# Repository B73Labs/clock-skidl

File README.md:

# Skidl + KiCad + Freerouting Clock Example

## TODO
- Replace Freerouting with programmatic routing

## Components

- WS2813 LEDs

## Programs
- Skidl 0.0.22
- KiCad
- Freerouting/LayoutEditor
- PyCharm Community

## Clock Generation

- Generate clock.net

`./clock.py`

- Load netlist into pcbnew
  - Open pcbnew
  - Tools > Load Netlist
  - Load clock.net
  - Select Re-associate footprints by reference (if required)
  - Update PCB
  - Close
  - Save pcb
  - Close pcbnew

- Generate layout
`./clock_place_leds.py`

- Export DSN for Freerouting
  - Open pcbnew
  - Export > Spectra DSN - `clock.dsn`
  
- Auto routing
  - Open freerouting
  - Open Your Own Design - `clock.dsn`
  - click Autorouter
  - get a coffee
  - File > Export Specctra Session File
  - File > Save and Exit  
  - Open pcbnew
  - File > Import > Specctra Session `clock.ses`
  
## Screenshot

## References

- [Skidl docs](https://xesscorp.github.io/skidl/docs/_site/index.html)
- [KiCad Scripting Reference](https://github.com/KiCad/kicad-doc/blob/master/src/pcbnew/pcbnew_python_scripting.adoc)
- [Python Scripting Example: Studio Clock](https://forum.kicad.info/t/python-scripting-example-studio-clock/5387)
- Kevin Cuzner [Arranging components in a circle with KiCad](http://kevincuzner.com/tag/pcbnew/)
- Studio Clock source - [KiCadStudioClock.zip](https://kicad-info.s3-us-west-2.amazonaws.com/original/2X/4/49e167315a677e95bbfc2e08c05e37a0b8d94dea.zip)
- Skidl: Blinkenface - [Others use it, too!](https://xesscorp.github.io/skidl/docs/_site/blog/others-use-it-too)
- Miles McCoo [KiCad Scripting blog](https://kicad.mmccoo.com/)
- Skidl: Studio Clock - [Two Easy Pieces](https://xesscorp.github.io/skidl/docs/_site/blog/two-easy-pieces)
- [LayoutEditor](http://www.layouteditor.net/)

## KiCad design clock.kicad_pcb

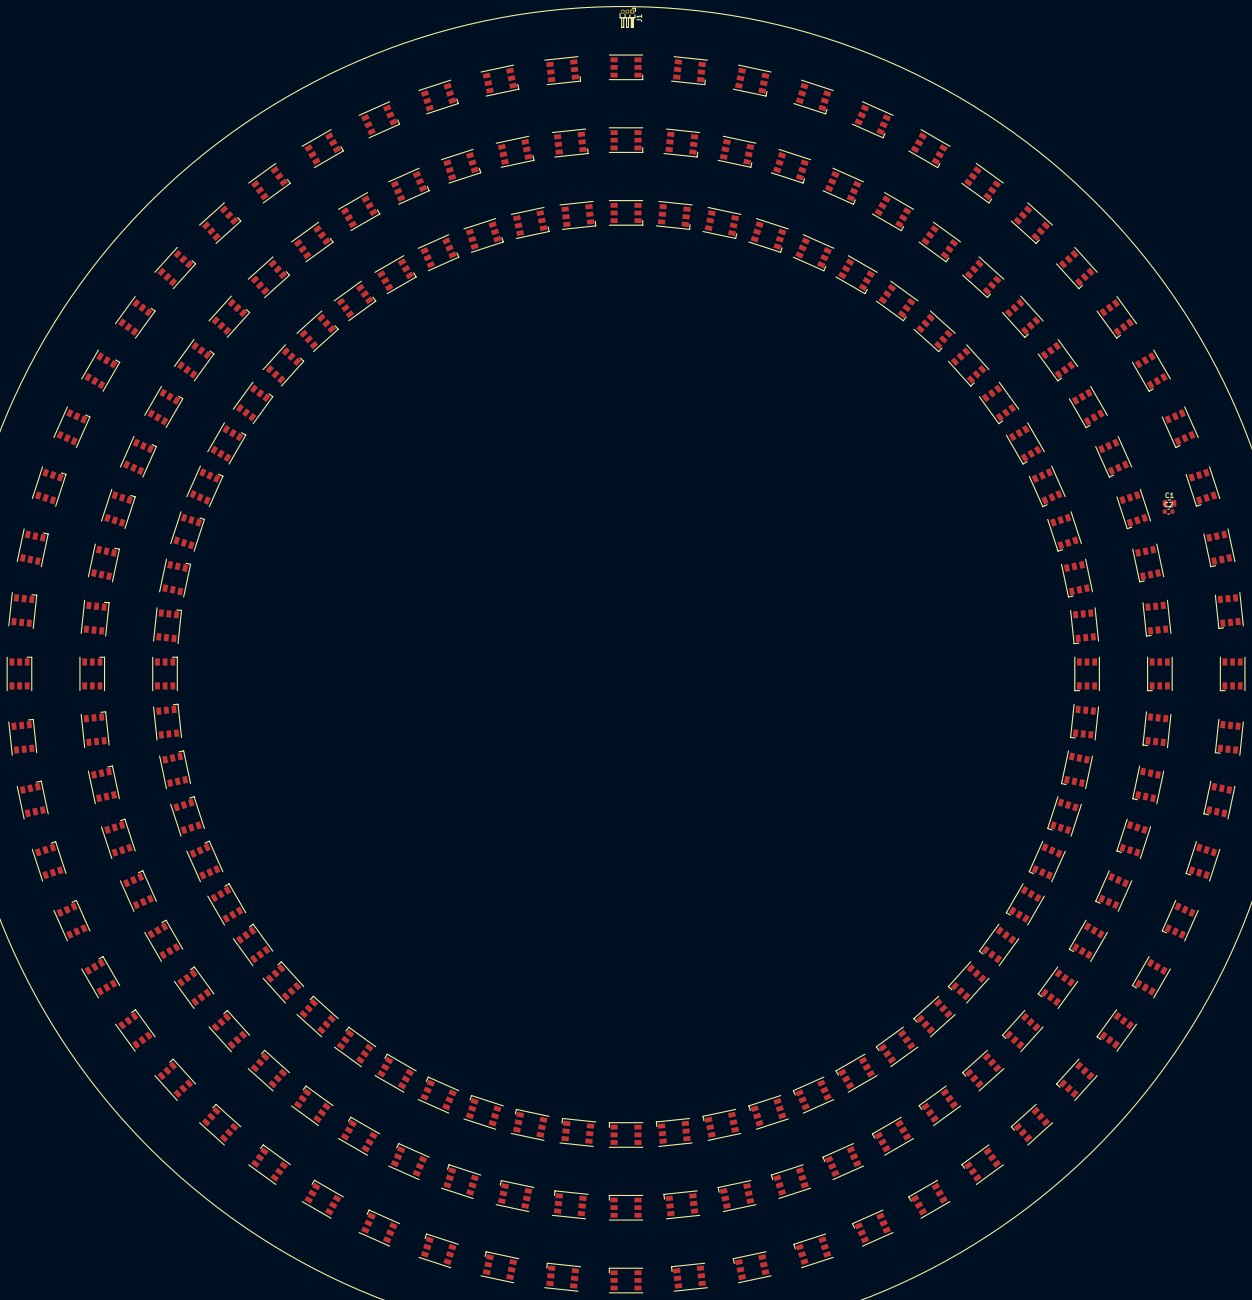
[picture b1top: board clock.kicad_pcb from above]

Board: 2 copper layers, 183 parts (0 on the bottom side), 182 nets, no tracks yet.

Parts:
C1: C; C_0805_2012Metric
C2: C; C_0603_1608Metric
D1, D2, D3, D4, D5, D6, D7, D8, D9, D10, D11, D12, D13, D14, D15, D16, D17, D18, D19, D20, D21, D22, D23, D24, D25, D26, D27, D28, D29, D30, D31, D32, D33, D34, D35, D36, D37, D38, D39, D40, D41, D42, D43, D44, D45, D46, D47, D48, D49, D50, D51, D52, D53, D54, D55, D56, D57, D58, D59, D60, D61, D62, D63, D64, D65, D66, D67, D68, D69, D70, D71, D72, D73, D74, D75, D76, D77, D78, D79, D80, D81, D82, D83, D84, D85, D86, D87, D88, D89, D90, D91, D92, D93, D94, D95, D96, D97, D98, D99, D100, D101, D102, D103, D104, D105, D106, D107, D108, D109, D110, D111, D112, D113, D114, D115, D116, D117, D118, D119, D120, D121, D122, D123, D124, D125, D126, D127, D128, D129, D130, D131, D132, D133, D134, D135, D136, D137, D138, D139, D140, D141, D142, D143, D144, D145, D146, D147, D148, D149, D150, D151, D152, D153, D154, D155, D156, D157, D158, D159, D160, D161, D162, D163, D164, D165, D166, D167, D168, D169, D170, D171, D172, D173, D174, D175, D176, D177, D178, D179, D180: WS2813; LED_Normandled_WS2813-06_5.0x5.0mm_Pitch1.6mm
J1: Conn_01x03; PinHeader_1x03_P1.00mm_Horizontal

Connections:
DOUT0: D1.4, D1.6, D2.6, J1.3
DOUT1: D1.3, D2.4, D3.6
DOUT2: D2.3, D3.4, D4.6
DOUT3: D3.3, D4.4, D5.6
DOUT4: D4.3, D5.4, D6.6
DOUT5: D5.3, D6.4, D7.6
DOUT6: D6.3, D7.4, D8.6
DOUT7: D7.3, D8.4, D9.6
DOUT8: D8.3, D9.4, D10.6
DOUT9: D9.3, D10.4, D11.6
DOUT10: D10.3, D11.4, D12.6
DOUT11: D11.3, D12.4, D13.6
DOUT12: D12.3, D13.4, D14.6
DOUT13: D13.3, D14.4, D15.6
DOUT14: D14.3, D15.4, D16.6
DOUT15: D15.3, D16.4, D17.6
DOUT16: D16.3, D17.4, D18.6
DOUT17: D17.3, D18.4, D19.6
DOUT18: D18.3, D19.4, D20.6
DOUT19: D19.3, D20.4, D21.6
DOUT20: D20.3, D21.4, D22.6
DOUT21: D21.3, D22.4, D23.6
DOUT22: D22.3, D23.4, D24.6
DOUT23: D23.3, D24.4, D25.6
DOUT24: D24.3, D25.4, D26.6
DOUT25: D25.3, D26.4, D27.6
DOUT26: D26.3, D27.4, D28.6
DOUT27: D27.3, D28.4, D29.6
DOUT28: D28.3, D29.4, D30.6
DOUT29: D29.3, D30.4, D31.6
DOUT30: D30.3, D31.4, D32.6
DOUT31: D31.3, D32.4, D33.6
DOUT32: D32.3, D33.4, D34.6
DOUT33: D33.3, D34.4, D35.6
DOUT34: D34.3, D35.4, D36.6
DOUT35: D35.3, D36.4, D37.6
DOUT36: D36.3, D37.4, D38.6
DOUT37: D37.3, D38.4, D39.6
DOUT38: D38.3, D39.4, D40.6
DOUT39: D39.3, D40.4, D41.6
DOUT40: D40.3, D41.4, D42.6
DOUT41: D41.3, D42.4, D43.6
DOUT42: D42.3, D43.4, D44.6
DOUT43: D43.3, D44.4, D45.6
DOUT44: D44.3, D45.4, D46.6
DOUT45: D45.3, D46.4, D47.6
DOUT46: D46.3, D47.4, D48.6
DOUT47: D47.3, D48.4, D49.6
DOUT48: D48.3, D49.4, D50.6
DOUT49: D49.3, D50.4, D51.6
DOUT50: D50.3, D51.4, D52.6
DOUT51: D51.3, D52.4, D53.6
DOUT52: D52.3, D53.4, D54.6
DOUT53: D53.3, D54.4, D55.6
DOUT54: D54.3, D55.4, D56.6
DOUT55: D55.3, D56.4, D57.6
DOUT56: D56.3, D57.4, D58.6
DOUT57: D57.3, D58.4, D59.6
DOUT58: D58.3, D59.4, D60.6
DOUT59: D59.3, D60.4, D61.6
DOUT60: D60.3, D61.4, D62.6
DOUT61: D61.3, D62.4, D63.6
DOUT62: D62.3, D63.4, D64.6
DOUT63: D63.3, D64.4, D65.6
DOUT64: D64.3, D65.4, D66.6
DOUT65: D65.3, D66.4, D67.6
DOUT66: D66.3, D67.4, D68.6
DOUT67: D67.3, D68.4, D69.6
DOUT68: D68.3, D69.4, D70.6
DOUT69: D69.3, D70.4, D71.6
DOUT70: D70.3, D71.4, D72.6
DOUT71: D71.3, D72.4, D73.6
DOUT72: D72.3, D73.4, D74.6
DOUT73: D73.3, D74.4, D75.6
DOUT74: D74.3, D75.4, D76.6
DOUT75: D75.3, D76.4, D77.6
DOUT76: D76.3, D77.4, D78.6
DOUT77: D77.3, D78.4, D79.6
DOUT78: D78.3, D79.4, D80.6
DOUT79: D79.3, D80.4, D81.6
DOUT80: D80.3, D81.4, D82.6
DOUT81: D81.3, D82.4, D83.6
DOUT82: D82.3, D83.4, D84.6
DOUT83: D83.3, D84.4, D85.6
DOUT84: D84.3, D85.4, D86.6
DOUT85: D85.3, D86.4, D87.6
DOUT86: D86.3, D87.4, D88.6
DOUT87: D87.3, D88.4, D89.6
DOUT88: D88.3, D89.4, D90.6
DOUT89: D89.3, D90.4, D91.6
DOUT90: D90.3, D91.4, D92.6
DOUT91: D91.3, D92.4, D93.6
DOUT92: D92.3, D93.4, D94.6
DOUT93: D93.3, D94.4, D95.6
DOUT94: D94.3, D95.4, D96.6
DOUT95: D95.3, D96.4, D97.6
DOUT96: D96.3, D97.4, D98.6
DOUT97: D97.3, D98.4, D99.6
DOUT98: D98.3, D99.4, D100.6
DOUT99: D99.3, D100.4, D101.6
DOUT100: D100.3, D101.4, D102.6
DOUT101: D101.3, D102.4, D103.6
DOUT102: D102.3, D103.4, D104.6
DOUT103: D103.3, D104.4, D105.6
DOUT104: D104.3, D105.4, D106.6
DOUT105: D105.3, D106.4, D107.6
DOUT106: D106.3, D107.4, D108.6
DOUT107: D107.3, D108.4, D109.6
DOUT108: D108.3, D109.4, D110.6
DOUT109: D109.3, D110.4, D111.6
DOUT110: D110.3, D111.4, D112.6
DOUT111: D111.3, D112.4, D113.6
DOUT112: D112.3, D113.4, D114.6
DOUT113: D113.3, D114.4, D115.6
DOUT114: D114.3, D115.4, D116.6
DOUT115: D115.3, D116.4, D117.6
DOUT116: D116.3, D117.4, D118.6
DOUT117: D117.3, D118.4, D119.6
DOUT118: D118.3, D119.4, D120.6
DOUT119: D119.3, D120.4, D121.6
DOUT120: D120.3, D121.4, D122.6
DOUT121: D121.3, D122.4, D123.6
DOUT122: D122.3, D123.4, D124.6
DOUT123: D123.3, D124.4, D125.6
DOUT124: D124.3, D125.4, D126.6
DOUT125: D125.3, D126.4, D127.6
DOUT126: D126.3, D127.4, D128.6
DOUT127: D127.3, D128.4, D129.6
DOUT128: D128.3, D129.4, D130.6
DOUT129: D129.3, D130.4, D131.6
DOUT130: D130.3, D131.4, D132.6
DOUT131: D131.3, D132.4, D133.6
DOUT132: D132.3, D133.4, D134.6
DOUT133: D133.3, D134.4, D135.6
DOUT134: D134.3, D135.4, D136.6
DOUT135: D135.3, D136.4, D137.6
DOUT136: D136.3, D137.4, D138.6
DOUT137: D137.3, D138.4, D139.6
DOUT138: D138.3, D139.4, D140.6
DOUT139: D139.3, D140.4, D141.6
DOUT140: D140.3, D141.4, D142.6
DOUT141: D141.3, D142.4, D143.6
DOUT142: D142.3, D143.4, D144.6
DOUT143: D143.3, D144.4, D145.6
DOUT144: D144.3, D145.4, D146.6
DOUT145: D145.3, D146.4, D147.6
DOUT146: D146.3, D147.4, D148.6
DOUT147: D147.3, D148.4, D149.6
DOUT148: D148.3, D149.4, D150.6
DOUT149: D149.3, D150.4, D151.6
DOUT150: D150.3, D151.4, D152.6
DOUT151: D151.3, D152.4, D153.6
DOUT152: D152.3, D153.4, D154.6
DOUT153: D153.3, D154.4, D155.6
DOUT154: D154.3, D155.4, D156.6
DOUT155: D155.3, D156.4, D157.6
DOUT156: D156.3, D157.4, D158.6
DOUT157: D157.3, D158.4, D159.6
DOUT158: D158.3, D159.4, D160.6
DOUT159: D159.3, D160.4, D161.6
DOUT160: D160.3, D161.4, D162.6
DOUT161: D161.3, D162.4, D163.6
DOUT162: D162.3, D163.4, D164.6
DOUT163: D163.3, D164.4, D165.6
DOUT164: D164.3, D165.4, D166.6
DOUT165: D165.3, D166.4, D167.6
DOUT166: D166.3, D167.4, D168.6
DOUT167: D167.3, D168.4, D169.6
DOUT168: D168.3, D169.4, D170.6
DOUT169: D169.3, D170.4, D171.6
DOUT170: D170.3, D171.4, D172.6
DOUT171: D171.3, D172.4, D173.6
DOUT172: D172.3, D173.4, D174.6
DOUT173: D173.3, D174.4, D175.6
DOUT174: D174.3, D175.4, D176.6
DOUT175: D175.3, D176.4, D177.6
DOUT176: D176.3, D177.4, D178.6
DOUT177: D177.3, D178.4, D179.6
DOUT178: D178.3, D179.4, D180.6
DOUT179: D179.3, D180.4
GND: C1.2, C2.2, D1.5, D2.5, D3.5, D4.5, D5.5, D6.5, D7.5, D8.5, D9.5, D10.5, D11.5, D12.5, D13.5, D14.5, D15.5, D16.5, D17.5, D18.5, D19.5, D20.5, D21.5, D22.5, D23.5, D24.5, D25.5, D26.5, D27.5, D28.5, D29.5, D30.5, D31.5, D32.5, D33.5, D34.5, D35.5, D36.5, D37.5, D38.5, D39.5, D40.5, D41.5, D42.5, D43.5, D44.5, D45.5, D46.5, D47.5, D48.5, D49.5, D50.5, D51.5, D52.5, D53.5, D54.5, D55.5, D56.5, D57.5, D58.5, D59.5, D60.5, D61.5, D62.5, D63.5, D64.5, D65.5, D66.5, D67.5, D68.5, D69.5, D70.5, D71.5, D72.5, D73.5, D74.5, D75.5, D76.5, D77.5, D78.5, D79.5, D80.5, D81.5, D82.5, D83.5, D84.5, D85.5, D86.5, D87.5, D88.5, D89.5, D90.5, D91.5, D92.5, D93.5, D94.5, D95.5, D96.5, D97.5, D98.5, D99.5, D100.5, D101.5, D102.5, D103.5, D104.5, D105.5, D106.5, D107.5, D108.5, D109.5, D110.5, D111.5, D112.5, D113.5, D114.5, D115.5, D116.5, D117.5, D118.5, D119.5, D120.5, D121.5, D122.5, D123.5, D124.5, D125.5, D126.5, D127.5, D128.5, D129.5, D130.5, D131.5, D132.5, D133.5, D134.5, D135.5, D136.5, D137.5, D138.5, D139.5, D140.5, D141.5, D142.5, D143.5, D144.5, D145.5, D146.5, D147.5, D148.5, D149.5, D150.5, D151.5, D152.5, D153.5, D154.5, D155.5, D156.5, D157.5, D158.5, D159.5, D160.5, D161.5, D162.5, D163.5, D164.5, D165.5, D166.5, D167.5, D168.5, D169.5, D170.5, D171.5, D172.5, D173.5, D174.5, D175.5, D176.5, D177.5, D178.5, D179.5, D180.5, J1.1
VDD: C1.1, C2.1, D1.2, D2.2, D3.2, D4.2, D5.2, D6.2, D7.2, D8.2, D9.2, D10.2, D11.2, D12.2, D13.2, D14.2, D15.2, D16.2, D17.2, D18.2, D19.2, D20.2, D21.2, D22.2, D23.2, D24.2, D25.2, D26.2, D27.2, D28.2, D29.2, D30.2, D31.2, D32.2, D33.2, D34.2, D35.2, D36.2, D37.2, D38.2, D39.2, D40.2, D41.2, D42.2, D43.2, D44.2, D45.2, D46.2, D47.2, D48.2, D49.2, D50.2, D51.2, D52.2, D53.2, D54.2, D55.2, D56.2, D57.2, D58.2, D59.2, D60.2, D61.2, D62.2, D63.2, D64.2, D65.2, D66.2, D67.2, D68.2, D69.2, D70.2, D71.2, D72.2, D73.2, D74.2, D75.2, D76.2, D77.2, D78.2, D79.2, D80.2, D81.2, D82.2, D83.2, D84.2, D85.2, D86.2, D87.2, D88.2, D89.2, D90.2, D91.2, D92.2, D93.2, D94.2, D95.2, D96.2, D97.2, D98.2, D99.2, D100.2, D101.2, D102.2, D103.2, D104.2, D105.2, D106.2, D107.2, D108.2, D109.2, D110.2, D111.2, D112.2, D113.2, D114.2, D115.2, D116.2, D117.2, D118.2, D119.2, D120.2, D121.2, D122.2, D123.2, D124.2, D125.2, D126.2, D127.2, D128.2, D129.2, D130.2, D131.2, D132.2, D133.2, D134.2, D135.2, D136.2, D137.2, D138.2, D139.2, D140.2, D141.2, D142.2, D143.2, D144.2, D145.2, D146.2, D147.2, D148.2, D149.2, D150.2, D151.2, D152.2, D153.2, D154.2, D155.2, D156.2, D157.2, D158.2, D159.2, D160.2, D161.2, D162.2, D163.2, D164.2, D165.2, D166.2, D167.2, D168.2, D169.2, D170.2, D171.2, D172.2, D173.2, D174.2, D175.2, D176.2, D177.2, D178.2, D179.2, D180.2, J1.2

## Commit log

2018-08-02 Example project using KiCad + Skidl + Freerouting - initial commit - automatic netlist generator - automatic circle placement script - python requirements - README file - WS2813 documentation
2018-08-02 - add screenshot
2018-08-02 - add screenshot to README
2018-08-02 - re-arrange references
